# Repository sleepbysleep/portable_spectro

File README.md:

# Introduction
I just want to make new kind of portable spectrometer, which would be equipped with more-efficient LED illumination ranging from 400nm to 1000nm than Tungsten-Hallogen lamp. The design intends to be switchable between two kinds of miniatured spectrometer(i.e. C12880MA, and ADS8860IDGS) for flexiblity. Indeed, the main controller should handle BlueTooth communication with intermediate device like smart phone or personal computer in order to gather the spectrum data into remote server.

In terms of Vis/NIR radiation, the useful choices are so-called braodband IR LED like SFH4736, SFH4776, and L1IG-0750100000000. Unfortunately, these things doesn't emit visible light except for violet band, which intends to make a phosper excited. So, I have to make the lighting in the combination of Vis LED and such a broadband LEDs. To accomplish proper illumination, many things have to be solved in aspects of blending ratio of Vis, and NIR, and how many LEDs are mounted on PCB for sufficient lighting. Therefore, the below have to be done;

1. Analyze the comparision of spectral intensity among SFH4736, SFH4776, and L1IG-0750100000000.
2. Determine blending ratio of Vis, and NIR LEDs for flatness of spectral intensity from Vis to NIR.
3. Design the hardware that can equip with nRF52840, Vis/NIR LEDs (corresponding driver as well), switchable spectrometer (corresponding periphertal indeed), and power management unit including Li-ion or Li-po battery, charging part, and boost regulator.
4. Develop the firmware that can process the BlueTooth communication with smart phone (iOS, and Android), interfacing the spectrometer, and interactive operation between LED-based illumination, and spectrometer.
5. Develop the application for iOS, and Android that can be portal to pass, and signal process the spectrum into the remote server.
6. Develop the remote server program, that can manage huge spectra with extra infomation (i.e. object, date, dependant like sugar content), and do machine learning, initially being PLS, and SVM-regression hopefully I want to goes into Deap Learning (CNN or RNN).

Definitly, all the staffs are very challenging to me in terms of funding, and workloads. I will do as much as possible!

# Hardware
The hardware consists of Li-ion or Li-po battery, charging unit, boost regulator, C12880MA spectrometer including analog amplifier, and ADC unit, AS7260X spectrometer, and nRF52840 BlueTooth CPU.

TODO: Block diagram

The schematic of ADS8860IDGS is referred from https://www.ti.com/lit/df/tidrau9a/tidrau9a.pdf
TODO: add image with highlight of the copied.

The schematic of C12880MA is referred from https://github.com/Alexey-Danilchenko/Spectron
TODO: add image with highlight of the copied

The schematic of AS7260x is referred from

The schematic of MCP73871 is referred from 

# Mechanical Drawing

# Spectral intesity comparison
TODO: add the graph among them.

# Firmware Design
openocd, my budget is the stlink v2
TODO: add Flow chart
TODO: add block diagram

# Integration time calculation

# App Design

# Server Design

# BOM
Spectrometer: C12880MA, or AS7260x be switchable
CPU: nrf52840, mdbt501-v10
Candidators for Light source: SFH4736, or SFH4776, or L1IG-0750100000000

# References
https://github.com/Alexey-Danilchenko/Spectron

# Appendix

## nRF52840 development environment

Install Toolchain on debian testing(currently bulleseye)
$ apt install libnewlib-dev libstdc++-arm-none-eabi-newlib libnewlib-arm-none-eabi gcc-arm-none-eabi binutils-arm-none-eabi

Verify the version of installed gcc
$ arm-none-eabi-gcc --version
arm-none-eabi-gcc (15:7-2018-q2-6+b1) 7.3.1 20180622 (release) [ARM/embedded-7-branch revision 261907]
Copyright (C) 2017 Free Software Foundation, Inc.
This is free software; see the source for copying conditions.  There is NO
warranty; not even for MERCHANTABILITY or FITNESS FOR A PARTICULAR PURPOSE.

Download, and install the nRF5 SDK
Go to https://www.nordicsemi.com/Software-and-Tools/Software/nRF5-SDK/, and
download the latest verion of SDK at https://www.nordicsemi.com/-/media/Software-and-other-downloads/SDKs/nRF5/Binaries/nRF5_SDK_16.0.0_98a08e2.zip
Unzip nRF5_SDK_16.0.0_98a08e2.zip like as:
nRF5_SDK_16.0.0_98a08e2
+- components
+- config
+- documentation
+- examples
+- external
+- external_tools
+- intergation
+- modules
+- license.txt
+- nRF5x_MDK_8_27_0_IAR_NordicLicense.msi
+- nRF5x_MDK_8_27_0_Keil4_NordicLicense.msi

At "$(SDK_ROOT)/components/toolchain/gcc" under SDK, there are several kinds of Makefile for Windows/Linux/MacOs.
Now, we should edit "Makefile.posix" in the case of Linux or MacOs like the below.

GNU_INSTALL_ROOT ?= /usr/local/gcc-arm-none-eabi-7-2018-q2-update/bin/
GNU_VERSION ?= 7.3.1
GNU_PREFIX ?= arm-none-eabi

into

GNU_INSTALL_ROOT ?= /usr/bin/
GNU_VERSION ?= 7.3.1
GNU_PREFIX ?= arm-none-eabi

Try to compile the example.
Under "$(SDK_ROOT)/examples/peripheral/blinky/PCA10056/blank/armgcc", 
$ make
mkdir _build
cd _build && mkdir nrf52840_xxaa
Assembling file: gcc_startup_nrf52840.S
Compiling file: nrf_log_frontend.c
Compiling file: nrf_log_str_formatter.c
Compiling file: boards.c
Compiling file: app_error.c
Compiling file: app_error_handler_gcc.c
Compiling file: app_error_weak.c
Compiling file: app_util_platform.c
Compiling file: nrf_assert.c
Compiling file: nrf_atomic.c
Compiling file: nrf_balloc.c
Compiling file: nrf_fprintf.c
Compiling file: nrf_fprintf_format.c
Compiling file: nrf_memobj.c
Compiling file: nrf_ringbuf.c
Compiling file: nrf_strerror.c
Compiling file: nrfx_atomic.c
Compiling file: main.c
Compiling file: system_nrf52840.c
Linking target: _build/nrf52840_xxaa.out
   text	   data	    bss	    dec	    hex	filename
   2168	    112	    172	   2452	    994	_build/nrf52840_xxaa.out
Preparing: _build/nrf52840_xxaa.hex
Preparing: _build/nrf52840_xxaa.bin
DONE nrf52840_xxaa

## Install programmer for nRF52, and setup correspondances
Download nRF Command Line Tools via https://www.nordicsemi.com/Software-and-tools/Development-Tools/nRF-Command-Line-Tools/Download#infotabs
In my case of Debian Linux(), the nRF-Command-Line-Tools_10_5_0_Linux-amd64.tar.gz is appropriate.

If you want to generate DFU formatted binary, please see the nRF-Utils for desktop at https://www.nordicsemi.com/Software-and-tools/Development-Tools/nRF-Util. Its actual location is https://github.com/NordicSemiconductor/pc-nrfutil. It isn't dependent from installed OS due to python package.

## Make the new project
Make new directory named as "projects" under the root of SDK.
$ mkdir projects
$ cd projects
$ mkdir template
$ cd ../

Copy files from main.c at examples/peripheral/bliky/, blinky_gcc_nrf52.ld, and Makefile at examples/peripheral/blinky/pca10056/blank/armgcc, and config/sdk_config.h at examples/peripheral/blinky/pca10056/blank into newly created project of projects/template.

$ cp -r ./examples/peripheral/blinky/main.c ./examples/peripheral/blinky/pca10056/blank/armgcc/blinky_gcc_nrf52.ld ./examples/peripheral/blinky/pca10056/blank/armgcc/Makefile ./examples/peripheral/blinky/pca10056/blank/config ./projects/template

Change some definitions in Makefile like;

SDK_ROOT := ../../../../../..
PROJ_DIR := ../../..
...
INC_FOLDERS += \
  $(SDK_ROOT)/components \
  $(SDK_ROOT)/modules/nrfx/mdk \
  $(PROJ_DIR) \
  $(SDK_ROOT)/components/libraries/strerror \
  $(SDK_ROOT)/components/toolchain/cmsis/include \
  $(SDK_ROOT)/components/libraries/util \
  ../config \
...
CFLAGS += -Wall -Werror
as

SDK_ROOT := ../..
PROJ_DIR := .
...
INC_FOLDERS += \
  $(SDK_ROOT)/components \
  $(SDK_ROOT)/modules/nrfx/mdk \
  $(PROJ_DIR) \
  $(SDK_ROOT)/components/libraries/strerror \
  $(SDK_ROOT)/components/toolchain/cmsis/include \
  $(SDK_ROOT)/components/libraries/util \
  ./config \
...
CFLAGS += -Wall #-Werror

Finally, make sure the compilation done.
daysleep@t480s-debian ~/W/p/f/p/template> make
mkdir _build
cd _build && mkdir nrf52840_xxaa
Assembling file: gcc_startup_nrf52840.S
Compiling file: nrf_log_frontend.c
Compiling file: nrf_log_str_formatter.c
Compiling file: boards.c
Compiling file: app_error.c
Compiling file: app_error_handler_gcc.c
Compiling file: app_error_weak.c
Compiling file: app_util_platform.c
Compiling file: nrf_assert.c
Compiling file: nrf_atomic.c
Compiling file: nrf_balloc.c
Compiling file: nrf_fprintf.c
Compiling file: nrf_fprintf_format.c
Compiling file: nrf_memobj.c
Compiling file: nrf_ringbuf.c
Compiling file: nrf_strerror.c
Compiling file: nrfx_atomic.c
Compiling file: main.c
Compiling file: system_nrf52840.c
Linking target: _build/nrf52840_xxaa.out
   text	   data	    bss	    dec	    hex	filename
   2168	    112	    172	   2452	    994	_build/nrf52840_xxaa.out
Preparing: _build/nrf52840_xxaa.hex
Preparing: _build/nrf52840_xxaa.bin
DONE nrf52840_xxaa

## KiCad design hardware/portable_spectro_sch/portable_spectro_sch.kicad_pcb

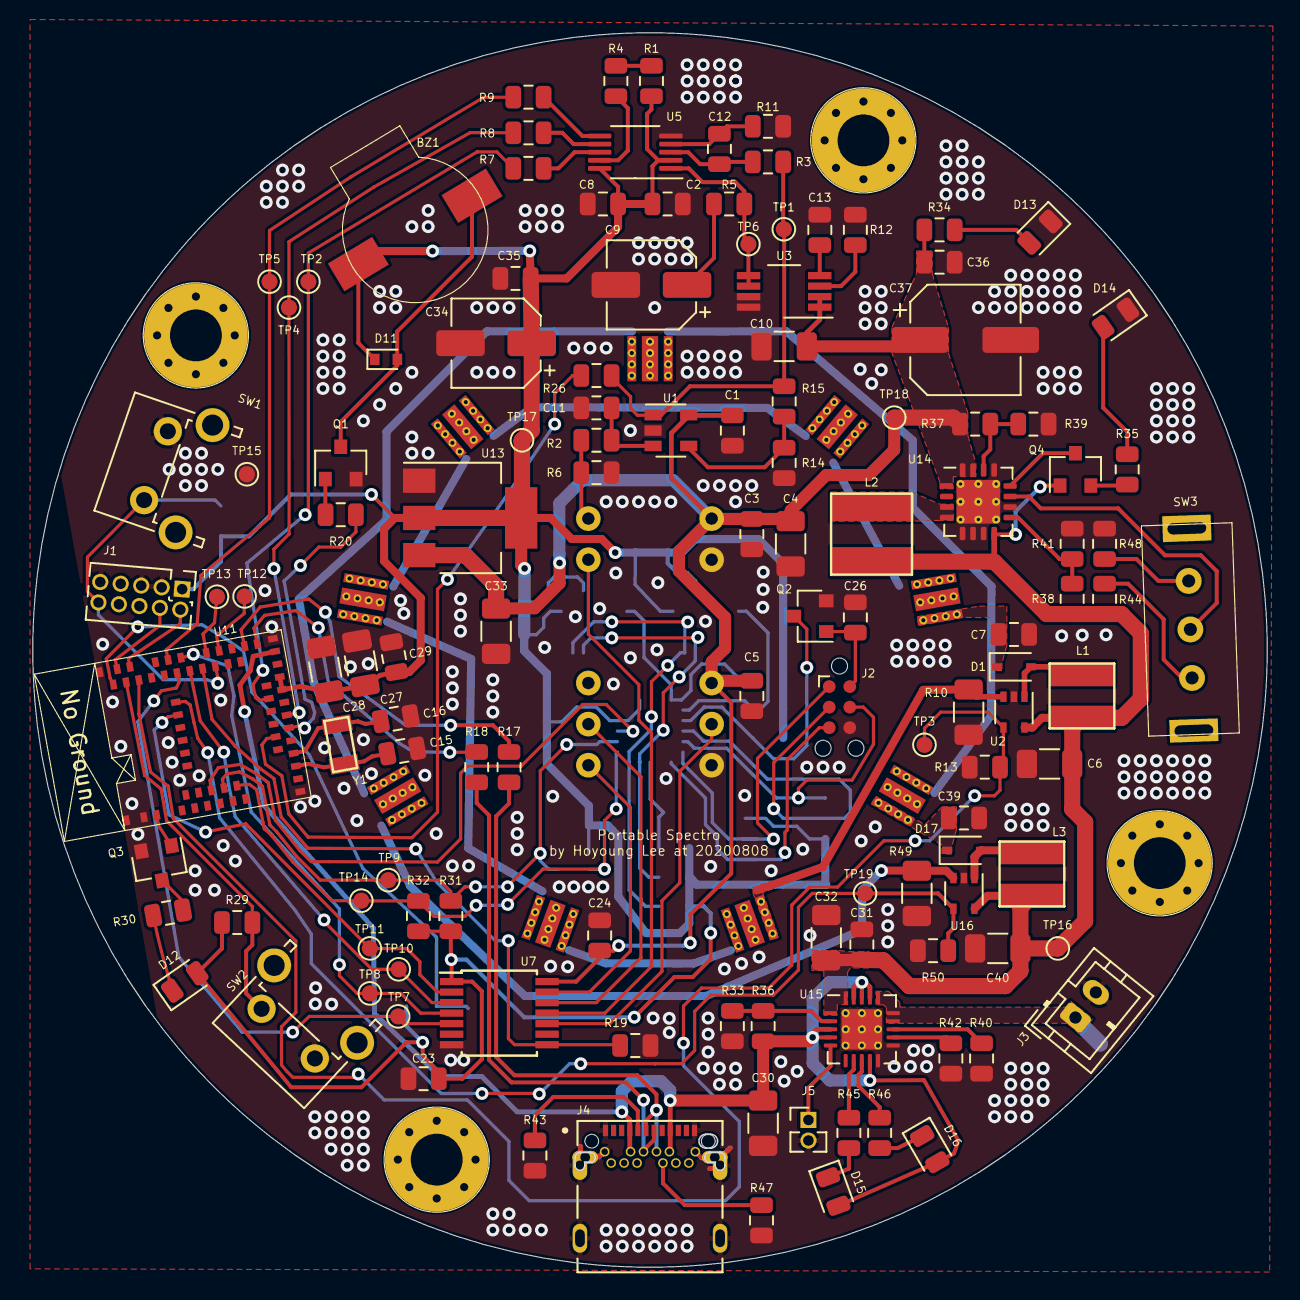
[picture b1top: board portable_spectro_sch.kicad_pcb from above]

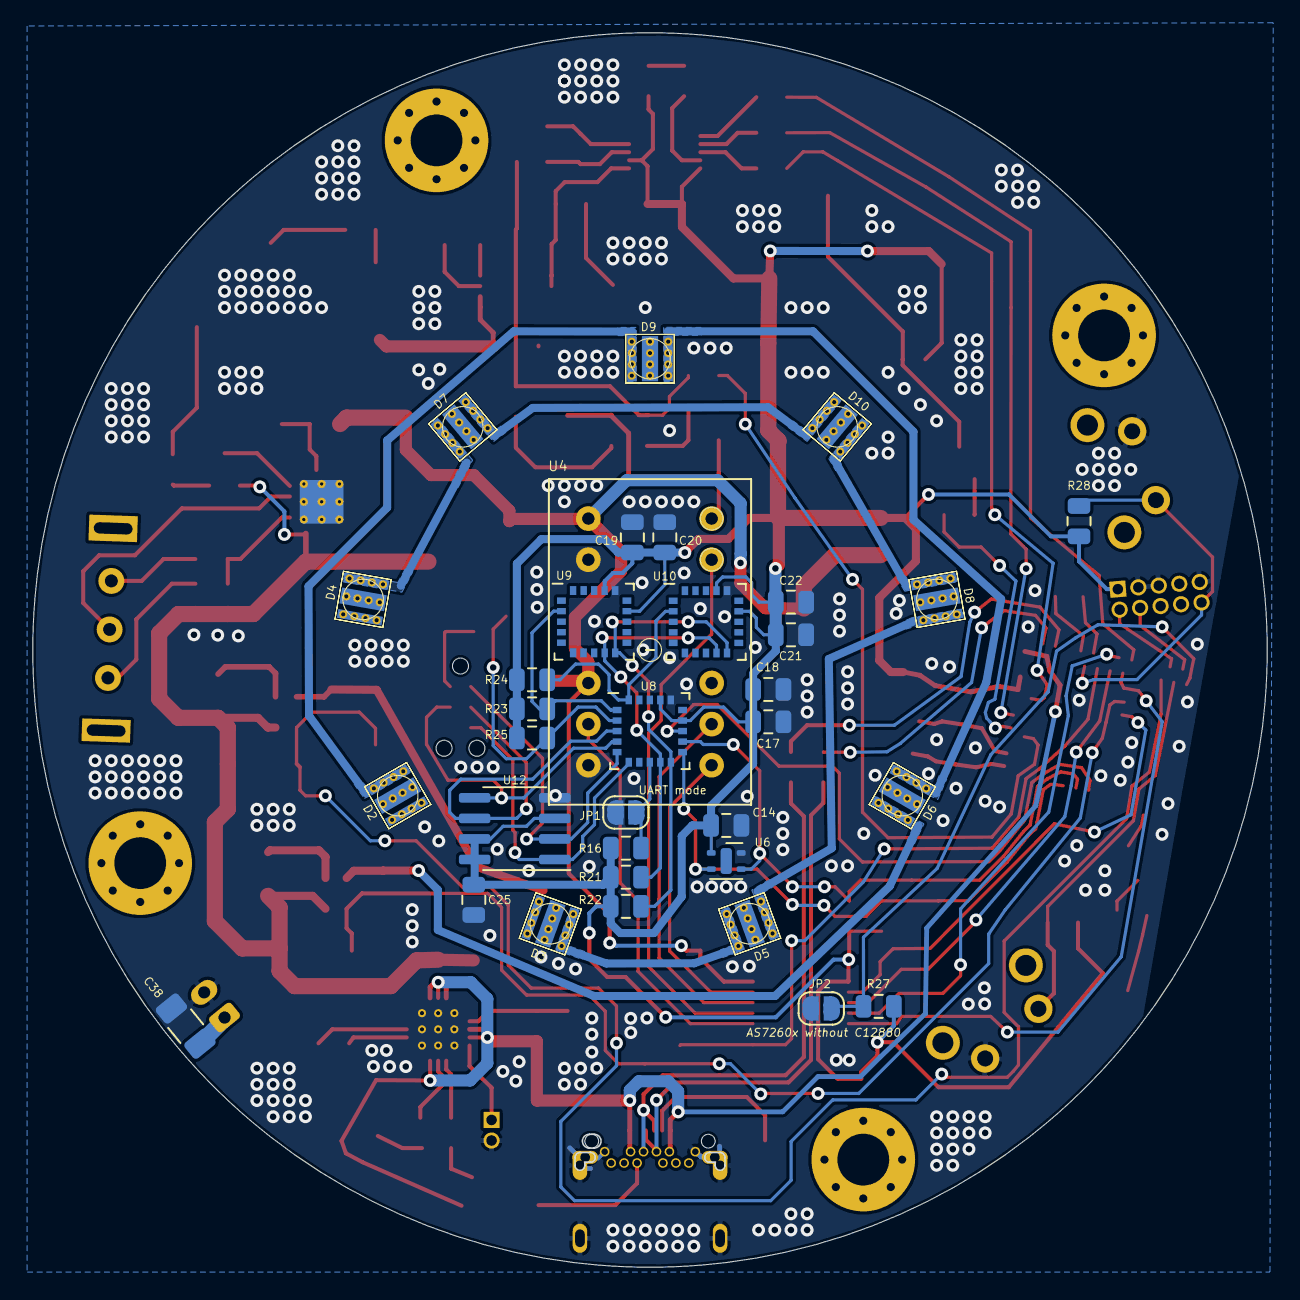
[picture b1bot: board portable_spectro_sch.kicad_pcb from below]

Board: 2 copper layers, 76.3 x 76.3 mm, 161 parts (34 on the bottom side), 102 nets.

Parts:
BZ1: CMT-0926-86-SMT-TR; Buzzer_CUI_CMT-0926-86-SMT-TR
C1, C5, C14, C17, C19, C21, C23, C24, C26, C29, C31: 0.1uF; C_0805_2012Metric
C2, C8, C13, C18, C20, C22, C25: 1uF; C_0805_2012Metric
C3, C35: 1000pF; C_0805_2012Metric
C4, C10, C27, C28, C32, C33, C38: 10uF; C_1206_3216Metric
C6, C40: 4.7uF/5V; C_1206_3216Metric
C7, C39: 1uF/40V; C_0805_2012Metric
C9: 47uF; CP_Elec_5x5.4
C11: N/A; C_0805_2012Metric
C12: 470pF; C_0805_2012Metric
C15, C16: 12.5pF; C_0805_2012Metric
C30: 10uF/10V; C_1206_3216Metric
C34: 10uF; CP_Elec_5x5.4
C36: 2.2uF; C_0805_2012Metric
C37: 100uF; CP_Elec_6.3x5.4
D1, D17: NSR0240; D_SOD-323
D2, D6, D9: GWCSSRM2.CM; LED-GWCSSRM2.CM_OSRAM-thermalvia
D3, D4, D5, D7, D8, D10: SFH4736; LED-GWCSSRM2.CM_OSRAM-thermalvia
D11: 1N4148WT; D_SOD-523
D12, D13, D14: Red; D_0805_2012Metric
D15: Green; D_0805_2012Metric
D16: Yellow; D_0805_2012Metric
J1: ARM_JTAG_SWD_10; PinHeader_2x05_P1.27mm_Vertical
J2: TC2030-NL; Tag-Connect_TC2030-IDC-NL_2x03_P1.27mm_Vertical
J3: Li-ion(1S2P); JST_PH_B2B-PH-K_1x02_P2.00mm_Vertical
J4: UJ31-CH-3-SMT-TR; CUI_UJ31-CH-3-SMT-TR
J5: 10K(NTC); PinHeader_1x02_P1.27mm_Vertical
JP1: UART_ON; SolderJumper-2_P1.3mm_Open_RoundedPad1.0x1.5mm
JP2: C1288MA/AS7265x; SolderJumper-2_P1.3mm_Open_RoundedPad1.0x1.5mm
L1, L3: 4.7uH; L_Laird_TYS4030150M-10
L2: 6.8uH; L_Laird_TYS5040470M-10
Q1: MMBT3904; SOT-23
Q2: DTC113Z; SOT-23
Q3: BSS123; SOT-23
Q4: MMUN2133LT1G; SOT-23
R1: 20.0K; R_0805_2012Metric
R2: 10; R_0805_2012Metric
R3, R11: 34; R_0805_2012Metric
R4, R7, R9: 47.0; R_0805_2012Metric
R5: 0.005; R_0805_2012Metric
R6: 51; R_0805_2012Metric
R8, R15, R26: 0; R_0805_2012Metric
R10, R49: 0.43/0.25W; R_1206_3216Metric
R12: 0.22; R_0805_2012Metric
R13, R16, R19, R23, R24, R25, R27, R28, R29, R48, R50: 10K; R_0805_2012Metric
R14: N/A; R_0805_2012Metric
R17, R18: 27; R_0805_2012Metric
R20: 330; R_0805_2012Metric
R21, R22, R31, R32: 2.2K; R_0805_2012Metric
R30, R34, R35, R45, R46: 1K; R_0805_2012Metric
R33, R42: 100K; R_0805_2012Metric
R36: 270K; R_0805_2012Metric
R37, R38: 1.87M; R_0805_2012Metric
R39, R44: 200K; R_0805_2012Metric
R40: 1.0K; R_0805_2012Metric
R41: 340K; R_0805_2012Metric
R43, R47: 5.1K; R_0805_2012Metric
SW1: RESET; SW_Tactile_SPST_Angled_PTS645Vx39-2LFS
SW2: USER; SW_Tactile_SPST_Angled_PTS645Vx39-2LFS
SW3: SW_PWR; SW_E-Switch_EG1206_SPDT_Angled
TP1: VIDEO; TestPoint_Pad_D1.0mm
TP2: ADC_SCLK; TestPoint_Pad_D1.0mm
TP3: BNIR; TestPoint_Pad_D1.0mm
TP4: ADC_MISO; TestPoint_Pad_D1.0mm
TP5: ADC_CNV; TestPoint_Pad_D1.0mm
TP6: REF(+4.096V); TestPoint_Pad_D1.0mm
TP7: 1MHZ; TestPoint_Pad_D1.0mm
TP8: EOS; TestPoint_Pad_D1.0mm
TP9: TX_SDA; TestPoint_Pad_D1.0mm
TP10: TRG; TestPoint_Pad_D1.0mm
TP11: ST; TestPoint_Pad_D1.0mm
TP12: RX; TestPoint_Pad_D1.0mm
TP13: TX; TestPoint_Pad_D1.0mm
TP14: RX_SCL; TestPoint_Pad_D1.0mm
TP15: GND; TestPoint_Pad_D1.0mm
TP16: +BATT; TestPoint_Pad_D1.0mm
TP17: +3.3V; TestPoint_Pad_D1.0mm
TP18: +5V; TestPoint_Pad_D1.0mm
TP19: VIS; TestPoint_Pad_D1.0mm
U1: OPA320AIDBV; SOT-23-5
U2, U16: TPS61169DCKR; SOT-353_SC-70-5
U3: REF6041IDGKR; VSSOP-8_3.0x3.0mm_P0.65mm
U4: c12880ma; C12880MA
U5: ADS8860IDGS; VSSOP-10_3x3mm_P0.5mm
U6: SHTC3; Sensirion_DFN-4-1EP_2x2mm_P1mm_EP0.7x1.6mm
U7: TXB0104PW; TSSOP-14_4.4x5mm_P0.65mm
U8: AS72651; AS7265x_LGA-20_4.6x4.4_Pitch0.65mm
U9: AS72652; AS7265x_LGA-20_4.6x4.4_Pitch0.65mm
U10: AS72653; AS7265x_LGA-20_4.6x4.4_Pitch0.65mm
U11: MDBT50Q(nRF52840); MDBT50Q-nRF52840
U12: AT25SF041; SOIC-8_3.9x4.9mm_P1.27mm
U13: LM1117-3.3; SOT-223-3_TabPin2
U14: TPS61090; Texas_S-PVQFN-N16_EP2.7x2.7mm_ThermalVias
U15: MCP73871-2CC; QFN-20-1EP_4x4mm_P0.5mm_EP2.5x2.5mm
Y1: 32.768Khz; Crystal_SMD_Epson_FC-135-2Pin_3.2x2.5mm

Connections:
+3V3: BZ1.1, C2.2, C8.1, C14.1, C17.1, C18.1, C19.1, C20.1, C21.1, C22.1, C23.1, C25.2, C27.1, C28.1, C29.1, C34.1, C35.1, D11.1, D12.2, J1.1, R1.1, R16.1, R21.2, R22.2, R23.2, R24.2, R25.2, R27.1, R28.1, R29.1, R31.1, R32.1, TP17.1, U5.2, U5.10, U6.1, U7.1, U8.14, U8.17, U9.14, U9.17, U10.14, U10.17, U11.28, U11.30, U12.3, U12.7, U12.8, U13.2
+5V: C1.1, C3.1, C4.1, C5.2, C10.1, C24.1, C33.1, C36.2, C37.1, R34.1, R37.1, TP18.1, U1.5, U3.1, U3.2, U4.1, U4.3, U7.14, U13.3, U14.1, U14.15, U14.16
+BATT: C6.1, C31.2, C32.1, C40.1, L1.2, L2.1, L3.2, Q4.1, R38.1, R44.1, TP16.1, U2.5, U14.8, U15.1, U15.20, U16.5
/1MHZ: U4.4, U7.10
/ADC_CNV: R9.1, TP5.1, U11.46
/ADC_MISO: R8.1, TP4.1, U11.24
/ADC_SCLK: R7.1, TP2.1, U11.27
/ARDUINO_A2: R26.2, U11.21
/ASx_SCL: R21.1, U8.9, U9.9, U10.9
/ASx_SDA: R22.1, U8.10, U9.10, U10.10
/BNIR: R13.1, TP3.1, U2.4, U11.50
/BUZZ: R20.1, U11.22
/C12880_1MHZ: TP7.1, U7.5, U11.45
/C12880_EN: R19.2, U7.8, U11.42
/C12880_EOS: TP8.1, U7.4, U11.44
/C12880_ST: TP11.1, U7.2, U11.60
/C12880_TRG: TP10.1, U7.3, U11.43
/CHRG: R46.1, U15.8
/D+: J4.A6, J4.B6, R17.2
/D-: J4.A7, J4.B7, R18.2
/DONE: R45.1, U15.7
/EOS: U4.9, U7.11
/FLASH_MISO: J2.1, U8.5, U12.2
/FLASH_MOSI: J2.4, U8.4, U12.5
/FLASH_SCK: J2.3, U8.3, U12.6
/FLASH_~CS: J2.5, U8.6, U12.1
/LBO: Q4.3, U14.12
/P0.09: R29.2, SW2.2, U11.52
/P0.10: JP2.1, R27.2, U11.54
/P1.10: Q3.1, U11.3
/PWR_UP: SW3.2, U14.11
/REF(+4.096V): R5.1, TP6.1, U3.5, U3.6, U5.1
/SCL: R32.2, TP14.1, U6.2, U8.11, U11.13
/SDA: R31.2, TP9.1, U6.3, U8.12, U11.11
/ST: U4.6, U7.13
/SWDCLK: J1.4, U11.53
/SWDIO: J1.2, U11.51
/TRG: U4.7, U7.12
/UART_RX: TP12.1, U11.39
/UART_TX: TP13.1, U11.41
/VIDEO: R3.2, R15.1, R26.1, TP1.1, U1.1
/VIS: R50.1, TP19.1, U11.61, U16.4
/VLipo: C38.1, J3.1, U15.14, U15.15, U15.16
/~ASx_RST: Q2.3, R25.1, U8.2
/~INT: U8.13, U11.9
/~RESET: J1.10, R28.2, SW1.1, U11.40
/~SLV1: R23.1, U8.1, U9.2
/~SLV2: R24.1, U8.20, U10.2
GND: C1.2, C2.1, C3.2, C4.2, C5.1, C6.2, C7.2, C8.2, C9.2, C10.2, C11.1, C13.2, C14.2, C15.1, C16.1, C17.2, C18.2, C19.2, C20.2, C21.2, C22.2, C23.2, C24.2, C25.1, C26.1, C27.2, C28.2, C29.2, C30.2, C31.1, C32.2, C33.2, C34.2, C35.2, C36.1, C37.2, C38.2, C39.2, C40.2, D13.1, D14.1, J1.3, J1.5, J1.9, J2.6, J3.2, J4.A1, J4.A12, J4.B1, J4.B12, J4.SH1, J4.SH2, J4.SH3, J4.SH4, J4.SH5, J4.SH6, J5.2, JP1.1, JP2.2, Q1.2, Q2.2, Q3.2, R6.2, R10.2, R11.2, R12.2, R13.2, R14.2, R19.1, R33.2, R39.2, R40.2, R41.2, R42.2, R43.1, R47.1, R48.2, R49.2, R50.2, SW1.2, SW2.1, TP15.1, U1.2, U2.2, U3.7, U3.8, U4.2, U4.5, U5.5, U6.4, U7.7, U8.16, U9.16, U10.16, U11.1, U11.2, U11.15, U11.33, U11.55, U12.4, U13.1, U14.5, U14.6, U14.7, U14.10, U14.13, U14.17, U15.10, U15.11, U15.21, U16.2
unnamed: BZ1.2, D11.2, Q1.3
unnamed: C7.1, D1.1, D4.2
unnamed: C9.1, R5.2
unnamed: C11.2, R2.1, U1.3
unnamed: C12.1, R11.1, U5.4
unnamed: C12.2, R3.1, U5.3
unnamed: C13.1, U3.4
unnamed: C15.2, U11.17, Y1.1
unnamed: C16.2, U11.18, Y1.2
unnamed: C26.2, J2.2, Q2.1
unnamed: C39.1, D2.2, D17.1
unnamed: D1.2, L1.1, U2.1
unnamed: D2.1, D9.2
unnamed: D3.1, R10.1, U2.3
unnamed: D3.2, D5.1
unnamed: D4.1, D7.2
unnamed: D5.2, D8.1
unnamed: D6.1, R49.1, U16.3
unnamed: D6.2, D9.1
unnamed: D8.2, D10.1
unnamed: D7.1, D10.2
unnamed: D12.1, R30.1
unnamed: D13.2, R34.2
unnamed: D14.2, R35.2
unnamed: D15.1, R45.2
unnamed: D16.1, R46.2
unnamed: D17.2, L3.1, U16.1
unnamed: J4.A5, R43.2
unnamed: J4.B5, R47.2
unnamed: J5.1, U15.5
unnamed: JP1.2, R16.2, U8.8
unnamed: L2.2, U14.3, U14.4
unnamed: Q1.1, R20.2
unnamed: Q3.3, R30.2
unnamed: Q4.2, R35.1
unnamed: R1.2, R4.1
unnamed: R2.2, R6.1, U4.10
unnamed: R4.2, U5.9
unnamed: R7.2, U5.8
unnamed: R8.2, U5.7
unnamed: R9.2, U5.6
unnamed: R12.1, U3.3
unnamed: R14.1, R15.2, U1.4
unnamed: R17.1, U11.35
unnamed: R18.1, U11.34
unnamed: R33.1, R36.2, U15.2
unnamed: R37.2, R39.1, U14.14
unnamed: R38.2, R41.1, U14.9
unnamed: R40.1, U15.13
unnamed: R42.1, U15.12
unnamed: R44.2, SW3.3
unnamed: R48.1, SW3.1
VBUS: C30.1, D15.2, D16.2, J4.A4, J4.A9, J4.B4, J4.B9, R36.1, U11.32, U15.3, U15.4, U15.9, U15.17, U15.18, U15.19

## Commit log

2020-08-21 Initial uploading
    which includes some documents, and drawing & schematic describing the hardware.
